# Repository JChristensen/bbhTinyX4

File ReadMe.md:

# ATtinyX4 Breadboard Helper #
http://github.com/JChristensen/bbhTinyX4  
ReadMe file  
Jack Christensen Jan 2015  

## Introduction ##

ATtiny Breadboard Helpers are the easiest way to breadboard Atmel ATtiny24/44/84 and ATtiny25/45/85 micrcontrollers! These small boards contain everything needed to run an ATtiny microcontroller, including:
- ICSP header
- Filter and bypass capacitors
- Reset button with pullup resistor
- LED with current-limiting resistor

The Breadboard Helper breaks out all the MCU's pins to a header and also connects to the breadboard's power rails. Plug the Breadboard Helper into a breadboard, add power, connect a programmer, and the microcontroller is ready to go!

PC boards can be ordered [from OSH Park](https://www.oshpark.com/shared_projects/I1Z984Pi).  
A Bill of Materials with Mouser part numbers is part of this repo.

## Power Connection (see photos below)##

A two-pin header connects the Breadboard Helper to the breadboard's power rails. This header should be soldered ***either*** into the position labeled **"a"** ***or*** into the position labeled **"b"**.

Use position **"a"** for breadboards where the power rail holes line up with those in the main part of the breadboard (most full-size breadboards). Use position **"b"** for breadboards where the power rail holes are staggered between those in the main part of the breadboard (most half-size breadboards).

Observe polarity carefully and ***do not*** solder headers into both positions **"a"** and **"b"**, as the result will likely not fit into any breadboard!

## Arduino Pin Mapping ##

The 12-pin header is labeled with Arduino pin numbers 0-10 plus RESET, using the pin mapping from the [Arduino-Tiny core](https://code.google.com/p/arduino-tiny/). Other cores may be used with the Breadboard Helper but be aware that the pin mapping may be different. The AVR port and pin numbers are also labeled for easy reference.

The LED is connected to Arduino pin 6 or PA4 (ADC4/USCK/SCL/T1/PCINT4).

## Make the right power connection ##

Some breadboards have holes in the power rails that line up with those in the main part of the breadboard -- this is **Type "a"**.  

Some breadboards have holes in the power rails that are staggered between those in the main part of the breadboard -- this is **Type "b"**.  

Solder the two-pin power rail header into position **"a"** *or* position **"b"**, *NOT BOTH!*

Add power (observe polarity!), connect a programmer and the ATtiny is ready to go!

## CC BY-SA ##
"ATtinyX4 Breadboard Helper" by Jack Christensen is licensed under [CC BY-SA 4.0](http://creativecommons.org/licenses/by-sa/4.0/).

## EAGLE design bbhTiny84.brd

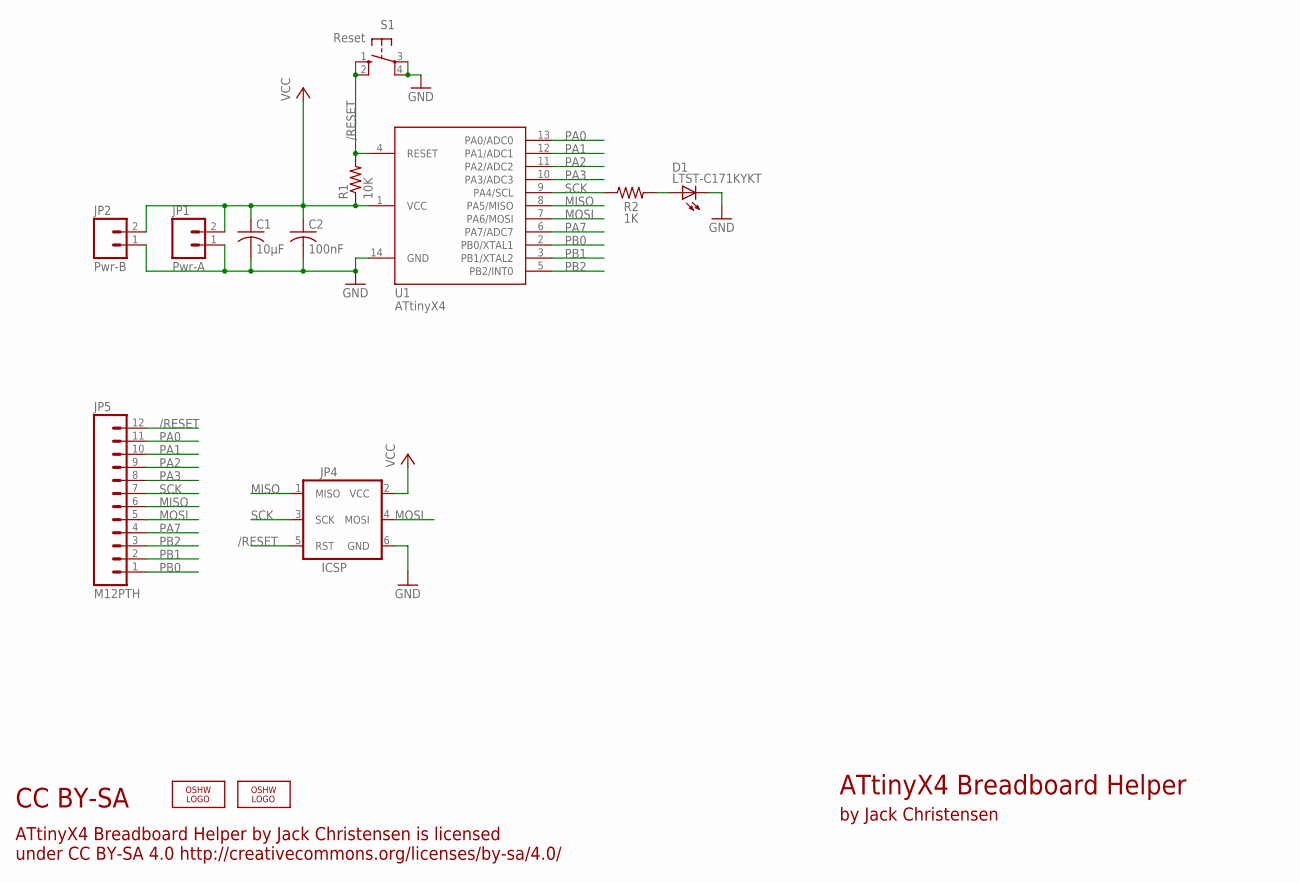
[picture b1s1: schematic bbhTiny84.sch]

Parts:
C1: 10µF; M0805
C2: 100nF; M0805
D1: LTST-C171KYKT; D0805
JP1: Pwr-A; 1X02
JP2: Pwr-B; 1X02
JP4: ICSP; 2X3_LOCK
JP5: M12PTH; 1X12
LOGO1, LOGO2: OSHW_LOGO_8MILX0100-NT; OSHW_8X100_NOTEXT
R1: 10K; M0805
R2: 1K; M0805
S1: Reset; B3F-10XXOCT
U1: ATtinyX4; DIL14

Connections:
/RESET: JP4.5 (RST), JP5.12, R1.2, S1.1 (S), S1.2 (S1), U1.4 (RESET)
GND: C1.2, C2.2, D1.K (C), JP1.1, JP2.1, JP4.6 (GND), S1.3, S1.4 (P1), U1.14 (GND)
MISO: JP4.1 (MISO), JP5.6, U1.8 (PA5/MISO)
MOSI: JP4.4 (MOSI), JP5.5, U1.7 (PA6/MOSI)
unnamed: D1.A, R2.2
PA0: JP5.11, U1.13 (PA0/ADC0)
PA1: JP5.10, U1.12 (PA1/ADC1)
PA2: JP5.9, U1.11 (PA2/ADC2)
PA3: JP5.8, U1.10 (PA3/ADC3)
PA7: JP5.4, U1.6 (PA7/ADC7)
PB0: JP5.1, U1.2 (PB0/XTAL1)
PB1: JP5.2, U1.3 (PB1/XTAL2)
PB2: JP5.3, U1.5 (PB2/INT0)
SCK: JP4.3 (SCK), JP5.7, R2.1, U1.9 (PA4/SCL)
VCC: C1.1, C2.1, JP1.2, JP2.2, JP4.2 (VCC), R1.1, U1.1 (VCC)

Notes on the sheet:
ATtinyX4 Breadboard Helper
by Jack Christensen
ATtinyX4 Breadboard Helper by Jack Christensen is licensed under CC BY-SA 4.0 http://creativecommons.org/licenses/by-sa/4.0/
CC BY-SA

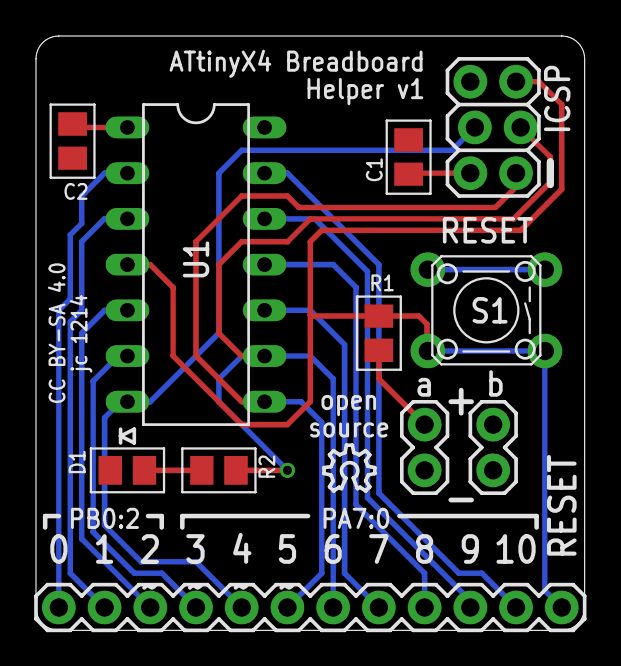
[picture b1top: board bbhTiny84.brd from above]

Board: 2 copper layers, 30.5 x 33.0 mm, 13 parts (1 on the bottom side), 15 nets.

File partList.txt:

Partlist

Exported from bbhTiny84.sch at 12/20/2014 8:45:01 AM

EAGLE Version 6.4.0 Copyright (c) 1988-2013 CadSoft

Assembly variant: 

Part     Value          Device                Package     Library  Sheet

C1       10µF           C-USM0805             M0805       _jc      1
C2       100nF          C-USM0805             M0805       _jc      1
D1       Yellow         LEDD0805              D0805       _jc      1
JP1      Pwr-A          M02PTH                1X02        SparkFun 1
JP2      Pwr-B          M02PTH                1X02        SparkFun 1
JP4      ICSP           AVR_SPI_PRG_62X3_LOCK 2X3_LOCK    _jc      1
JP5      M12PTH         M12PTH                1X12        SparkFun 1
R1       10K            R-US_M0805            M0805       _jc      1
R2       1K             R-US_M0805            M0805       _jc      1
S1       Reset          10-XXOCT              B3F-10XXOCT _jc      1
U1       ATtinyX4       ATTINYX4DIL14         DIL14       _jc      1

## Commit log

2015-01-07 Initial commit, v1.
2015-01-14 Add BOM, photos, update ReadMe & License files.
2015-01-14 Add board and schematic images.
2015-01-14 Image update.
2015-01-14 Update ReadMe.
2015-01-16 Adjust photos.

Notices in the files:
bbhTiny84.brd:
CC BY-SA 4.0 jc 1214
parts and their libraries:
SparkFun: Licensing: CC v3.0 Share-Alike You are welcome to use this library for commercial purposes.
